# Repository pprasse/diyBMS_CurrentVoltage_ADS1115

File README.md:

# diyBMS_CurrentVoltage_ADS1115

Isolated current and isolated voltage sensor for up to 850V & 200A based on ADS1115 and attiny1614 with isolated RS485 / MODBUS. (based on https://github.com/stuartpittaway/diyBMS-CurrentShunt)

# Current / Voltage measurement

The current measurement uses an ACS758ECB-200B hall-effect based current sensor IC.

The voltage measurement is isolated using an ACPL-C870 Precision Optically Isolated Voltage Sensor.

The analog signal from both measurements are converted using a ADS1115 16 bit ADC.

Coulomb calculation takes place in using an attiny1614 and communication uses isolated RS485 / MODBUS.

# Basis

The project is based on https://github.com/stuartpittaway/diyBMS-CurrentShunt and was created to allow using high voltage batteries for diyBMSv4.

# BOARD

The schematics and board are in the directory KiCad.

# CODE / FIRMWARE

The firmware in the directory code is losely based on Stuard Pittaway's diyBMS CurrentShunt. It uses the same MODBUS RTU registers.

## Coulomb calculation

The charge that goes in and out is calculated by sampling the current 128 times per second using the ADS1115 and measuring the time beween each sample. These are then integrated first to mA*ms (uAs) and then every second to mAh (milliamphours).

## Voltage measurement

The voltage is measured every 1 second as it's irrelevant for charge calculation but interesting for power calculation and over/undervoltage checks.

## MODBUS registers

See [MODBUS Registers.md](./code/MODBUS%20Registers.md)

Maximum compatibililty to diyBMS-CurrentShunt should be maintained to allow using the diyBMS4 ESP32 code unmodified.

Please note that due to compatibility the double registers are in mixed endian (floats compromised of 2 16bit registers in little endian, but individual 16 bit registers are big endian) BUT the 32bit integers are big endian.

Use [read-modbus.sh](./code/read-modbus.sh) ```# code/read-modbus.sh``` to read the modbus registers.

# WARNING

This is a DIY product/solution so don’t use this for safety critical systems or in any situation where there could be a risk to life.  

This board was designed to work with high DC voltages which are notoriously dangerous to work with and are a risk to life. Please make sure you have the appropriate knowledge and always use fuses specified for DC.

There is no warranty, it may not work as expected or at all.

The use of this project is done so entirely at your own risk.  It may involve electrical voltages which could kill - if in doubt, seek help.

The use of this project may not be compliant with local laws or regulations - if in doubt, seek help.

# License

This work is licensed under a Creative Commons Attribution-NonCommercial-ShareAlike 2.0 UK: England & Wales License.

https://creativecommons.org/licenses/by-nc-sa/2.0/uk/

You are free to:
* Share — copy and redistribute the material in any medium or format
* Adapt — remix, transform, and build upon the material
The licensor cannot revoke these freedoms as long as you follow the license terms.

Under the following terms:
* Attribution — You must give appropriate credit, provide a link to the license, and indicate if changes were made. You may do so in any reasonable manner, but not in any way that suggests the licensor endorses you or your use.
* Non-Commercial — You may not use the material for commercial purposes.
* ShareAlike — If you remix, transform, or build upon the material, you must distribute your contributions under the same license as the original.
* No additional restrictions — You may not apply legal terms or technological measures that legally restrict others from doing anything the license permits.

Notices:
You do not have to comply with the license for elements of the material in the public domain or where your use is permitted by an applicable exception or limitation.

No warranties are given. The license may not give you all of the permissions necessary for your intended use. For example, other rights such as publicity, privacy, or moral rights may limit how you use the material.

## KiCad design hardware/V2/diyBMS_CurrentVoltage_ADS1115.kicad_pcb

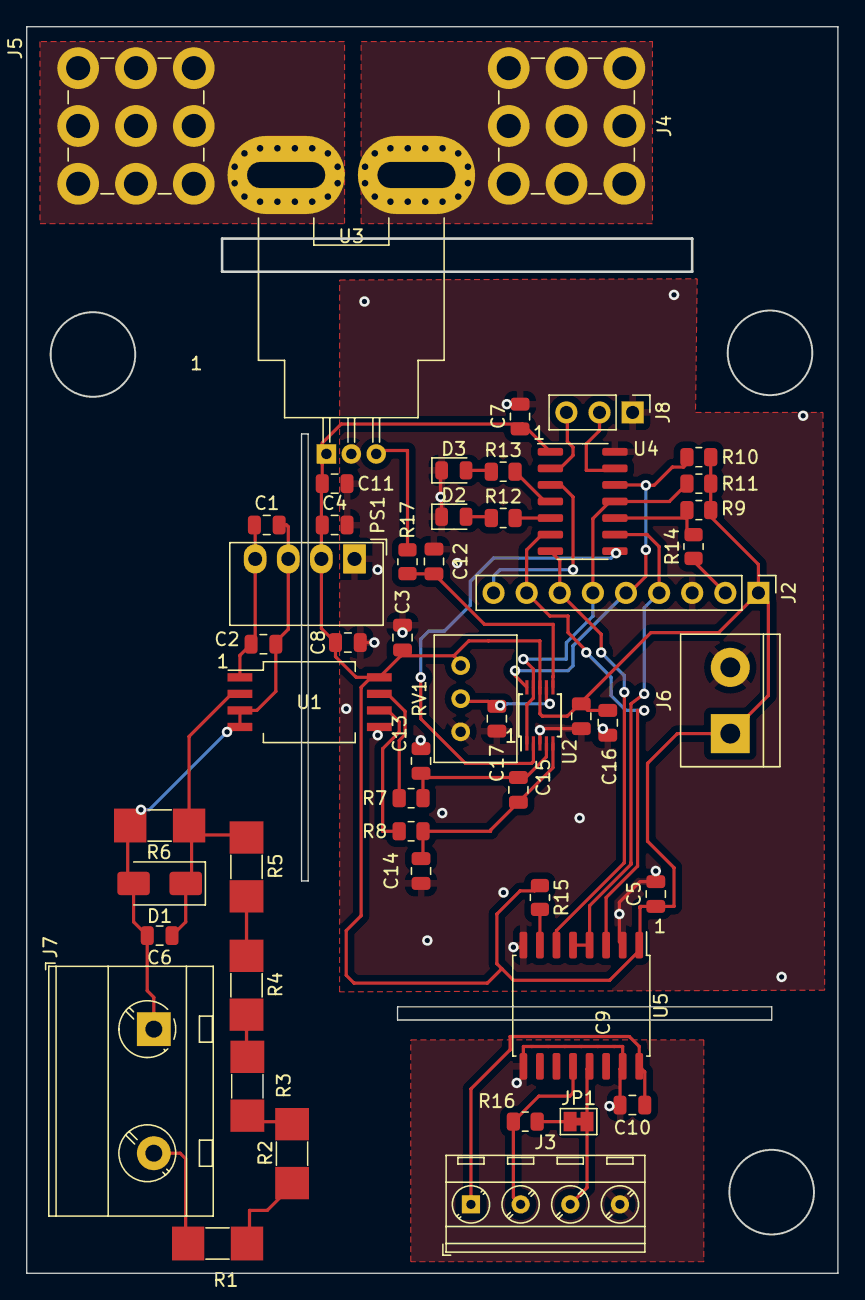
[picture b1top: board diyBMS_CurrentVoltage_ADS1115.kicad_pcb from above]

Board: 2 copper layers, 62.1 x 95.5 mm, 52 parts (0 on the bottom side), 40 nets.

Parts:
C1, C4, C7, C16: 10u; C_0805_2012Metric
C2, C3, C5, C11, C13, C14, C15: 100n; C_0805_2012Metric
C6: 1n; C_0805_2012Metric
C8, C9, C10: 100nF; C_0805_2012Metric
C12, C17: 100n 100V; C_0805_2012Metric
D1: SMAJ5.0A; D_SMA
D2: GREEN; LED_0805_2012Metric
D3: RED; LED_0805_2012Metric
J2: Debug/UPDI; PinHeader_1x09_P2.54mm_Vertical
J3: Screw_Terminal_01x04; TerminalBlock_MetzConnect_Type086_RT03404HBLC_1x04_P3.81mm_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
J4, J5: 9x9 PIN connector; Wuerth_REDCUBE-THR_WP-THRBU_74650194_THR
J6: Screw_Terminal_01x02; TerminalBlock_bornier-2_P5.08mm
J7: Screw_Terminal_01x02; TerminalBlock_MetzConnect_Type703_RT10N02HGLU_1x02_P9.52mm_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
J8: PA3/PA4; PinHeader_1x03_P2.54mm_Vertical
JP1: SolderJumper_2_Bridged; SolderJumper-2_P1.3mm_Bridged_Pad1.0x1.5mm
PS1: MEE1S0505SC; Converter_DCDC_Murata_MEE1SxxxxSC_THT
R1, R2, R3, R4, R5: 402k; PP | R_MELF_MMB-0207 | 0805 Compatible
R6: 4k7; PP | R_MELF_MMB-0207 | 0805 Compatible
R7, R8, R17: 10k; R_0805_2012Metric
R9: 100K; R_0805_2012Metric
R10, R11: 4k7; R_0805_2012Metric
R12, R13: 330R; R_0805_2012Metric
R14: 470R; R_0805_2012Metric
R15: 10K; R_0805_2012Metric
R16: 120R; R_0805_2012Metric
RV1: 10k 10turn; Potentiometer_Bourns_3299W_Vertical
U1: ACPL-C870; SSO-8_6.8x5.9mm_P1.27mm_Clearance8mm
U2: ADS1115IDGS; TSSOP-10_3x3mm_P0.5mm
U3: ACS758xCB-200B-PFF; Allegro_CB_PFF
U4: ATtiny1614-SS; SOIC-14_3.9x8.7mm_P1.27mm
U5: ADM2483xRW; SOIC-16W_7.5x10.3mm_P1.27mm

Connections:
+5V: C3.1, C4.1, C5.1, C7.1, C8.1, C9.1, C11.1, C16.2, J2.1, J6.1, PS1.2 (+Vin), R9.2, R10.1, R11.1, R15.1, RV1.1, U1.8 (VDD2), U2.8 (VDD), U3.1 (VCC), U4.1 (VCC), U5.1 (VDD1)
+5VP: C1.1, C2.1, PS1.4 (+Vout), U1.1 (VDD1)
A: J3.2, R16.2, U5.12 (A)
ALERT: U2.2 (ALERT/RDY), U4.8 (PB1)
B: J3.3, JP1.2 (B), U5.13 (B)
GND: C3.2, C4.2, C5.2, C7.2, C8.2, C9.2, C11.2, C12.2, C13.1, C14.2, C16.1, C17.2, D2.1 (K), D3.1 (K), J2.3, J6.2, J8.1, PS1.1 (-Vin), RV1.3, U1.5 (GND2), U2.3 (GND), U3.2 (GND), U4.14 (GND), U5.2 (GND1), U5.8 (GND1)
GND1: C1.2, C2.2, C6.2, D1.2 (A2), J7.1, PS1.3 (-Vout), R6.2, U1.3 (IN-), U1.4 (GND1)
GND2: C10.1, J3.4, U5.9 (GND2), U5.15 (GND2)
unnamed: C6.1, D1.1 (A1), R5.2, R6.1, U1.2 (IN)
unnamed: D2.2 (A), R12.1
unnamed: D3.2 (A), R13.1
unnamed: J2.2, R14.1
unnamed: J4.1, U3.4 (IP+)
unnamed: J5.1, U3.5 (IP-)
unnamed: J7.2, R1.1
unnamed: JP1.1 (A), R16.1
unnamed: R1.2, R2.1
unnamed: R2.2, R3.1
unnamed: R3.2, R4.1
unnamed: R4.2, R5.1
unnamed: R7.1, U1.7 (OUT+)
unnamed: R8.1, U1.6 (OUT-)
unnamed: C13.2, C15.2, R7.2, U2.4 (AIN0)
unnamed: C14.1, C15.1, R8.2, U2.5 (AIN1)
unnamed: C12.1, R17.1, U2.6 (AIN2)
unnamed: C17.1, RV1.2, U2.7 (AIN3)
unnamed: R17.2, U3.3 (VIOUT)
unnamed: R15.2, U5.7 (PV)
PA3: J8.2, U4.13 (PA3)
PA4: J8.3, U4.2 (PA4)
PA5: J2.9, U4.3 (PA5)
PA6: R13.2, U4.4 (PA6)
PA7: R12.2, U4.5 (PA7)
RESET: R9.1, R14.2, U4.10 (~RESET/PA0)
RXD: J2.8, U4.6 (PB3), U5.3 (RxD)
SCL: J2.5, R10.2, U2.10 (SCL), U4.12 (PA2)
SDA: J2.6, R11.2, U2.1 (ADDR), U2.9 (SDA), U4.11 (PA1)
TXD: J2.7, U4.7 (PB2), U5.6 (TxD)
VDD2: C10.2, J3.1, U5.16 (VDD2)
XDIR: J2.4, U4.9 (PB0), U5.4 (~RE), U5.5 (DE)

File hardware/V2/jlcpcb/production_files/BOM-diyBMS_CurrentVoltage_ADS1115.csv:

Comment,Designator,Footprint,LCSC
MEE1S0505SC,PS1,Converter_DCDC_Murata_MEE1SxxxxSC_THT,C131038
10u,"C1,C4",C_0805_2012Metric,C15850
ACS758xCB-200B-PFF,U3,Allegro_CB_PFF,C163288
100K,R9,R_0805_2012Metric,C17407
10K,"R15,R7,R8",R_0805_2012Metric,C17414
120R,R16,R_0805_2012Metric,C17437
330R,"R12,R13",R_0805_2012Metric,C17630
4k7,"R10,R11,R17",R_0805_2012Metric,C17673
470R,R14,R_0805_2012Metric,C17710
402k,"R1,R2,R3,R4,R5",PP | R_MELF_MMB-0207 | 0805 Compatible,C205375
GREEN,D2,LED_0805_2012Metric,C2297
10u,"C16,C7",C_0805_2012Metric,C28323
4k7,R6,PP | R_MELF_MMB-0207 | 0805 Compatible,C351460
ADS1115IDGS,U2,TSSOP-10_3x3mm_P0.5mm,C37593
ADM2483xRW,U5,SOIC-16W_7.5x10.3mm_P1.27mm,C386280
Screw_Terminal_01x04,J3,TerminalBlock_MetzConnect_Type086_RT03404HBLC_1x04_P3.81mm_Horizontal,C395880
100n 100V,C17,C_0805_2012Metric,C465471
1n,C6,C_0805_2012Metric,C46653
Screw_Terminal_01x02,J6,TerminalBlock_bornier-2_P5.08mm,C475092
ATtiny1614-SS,U4,SOIC-14_3.9x8.7mm_P1.27mm,C481364
100nF,"C10,C11,C12,C13,C14,C15,C2,C3,C5,C8,C9",C_0805_2012Metric,C49678
RED,D3,LED_0805_2012Metric,C84256
SMAJ5.0A,D1,D_SMA,C908198
Screw_Terminal_01x02,J7,TerminalBlock_MetzConnect_Type703_RT10N02HGLU_1x02_P9.52mm_Horizontal,C92145
9x9 PIN connector,J5,Wuerth_REDCUBE-THR_WP-THRBU_74650194_THR,
9x9 PIN connector,J4,Wuerth_REDCUBE-THR_WP-THRBU_74650194_THR,
ACPL-C870,U1,SSO-8_6.8x5.9mm_P1.27mm_Clearance8mm,

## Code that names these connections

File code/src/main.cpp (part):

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
void ConfigurePorts()
{
  // PA1 = SDA
  // PA2 = SCL
  // PA3 = UNUSED
  // PA4 = UNUSED
  // PA5 = RELAY OUTPUT
  // PA6 = RED LED
  // PA7 = GREEN LED

  // Set pins as Outputs (other pins are inputs)
  PORTA.DIR = GREENLED_PIN_BITMAP | REDLED_PIN_BITMAP | RELAY_PIN_BITMAP;
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  PORTA.OUTCLR = RELAY_PIN_BITMAP;

  // Set Port B digital outputs
  // PB0 = XDIR (RS485 transmit enable)
  // PB1 = ALERT
  // PB2 = TX (has to be set as output on tiny1614)
  // PB3 = RX
  // Set pins as Outputs (other pins are inputs)
  PORTB.DIR = PIN0_bm | PIN2_bm;

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{
  //When the transmitter is disabled, it will no longer override the TXD pin, and the pin
  //direction is automatically set as input by hardware, even if it was configured as output by the user
  //PB2 as OUTPUT
  PORTB.DIRSET = PIN2_bm;
  USART0.CTRLB |= USART_TXEN_bm; // Transmitter Enable bit mask.
}
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  GreenLED(false);
  EnableWatchdog();

  // Serial uses PB2/PB3 and PB0 for XDIR
  Serial.begin(ModBusBaudRate, MODBUSSERIALCONFIG);
  // leave XDIR on in every case as we can debug over RS485 using the compile define SERIALDEBUG
  // 0x01= Enables RS-485 mode with control of an external line driver through a dedicated Transmit Enable (TE) pin.
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
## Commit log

2023-08-07 progress but still untested
2023-08-26 progress
2023-08-27 working including MODBUS RTU
2023-08-27 modbus read script
2023-08-28 bitflags fixed
2023-08-28 eeprom carnary git version
2023-09-22 fix integration
2023-09-22 fix of the sign integration, leading to proper in/out mAh
2024-08-15 Added hardware V1, added trimmer to hardware V2, fixed parity between schematic & gerber

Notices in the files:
code/src/main.cpp:
(c)2023 Patrick Prasse
(c)2021 Stuart Pittaway
Attribution-NonCommercial-ShareAlike 2.0 UK: England & Wales (CC BY-NC-SA 2.0 UK)
